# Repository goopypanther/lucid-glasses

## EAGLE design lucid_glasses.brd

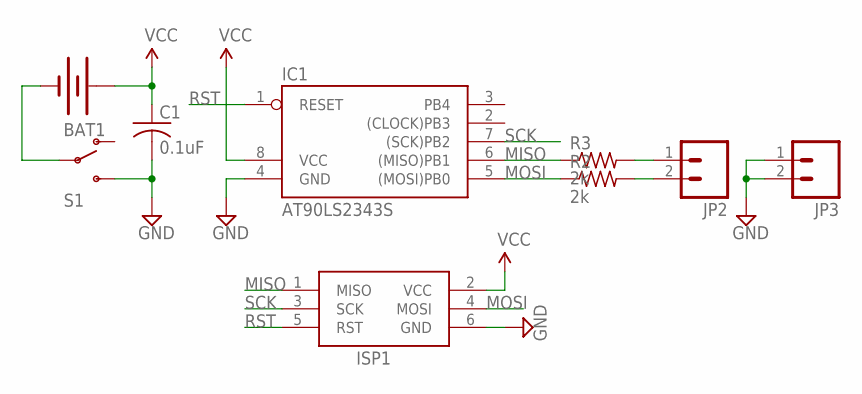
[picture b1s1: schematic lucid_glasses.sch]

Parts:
BAT1: BATTERY20SMD; BATTCON_20MM
C1: 0.1uF; C1206
IC1: AT90LS2343S; SOIC8
ISP1: AVRISP-6; AVRISP
JP2, JP3: M02PTH; 1X02
R2, R3: 2k; R1206
S1: SWITCH-SPSTSMD2; SWITCH-SPDT-SMD

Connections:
GND: C1.2, IC1.4 (GND), ISP1.6 (GND), JP3.1, JP3.2, S1.3 (S)
MISO: IC1.6 ((MISO)PB1), ISP1.1 (MISO), R3.1
MOSI: IC1.5 ((MOSI)PB0), ISP1.4 (MOSI), R2.1
unnamed: JP2.1, R3.2
unnamed: BAT1.2 (-), S1.2
unnamed: JP2.2, R2.2
RST: IC1.1 (RESET), ISP1.5 (RST)
SCK: IC1.7 ((SCK)PB2), ISP1.3 (SCK)
VCC: BAT1.1 (+), C1.1, IC1.8 (VCC), ISP1.2 (VCC)

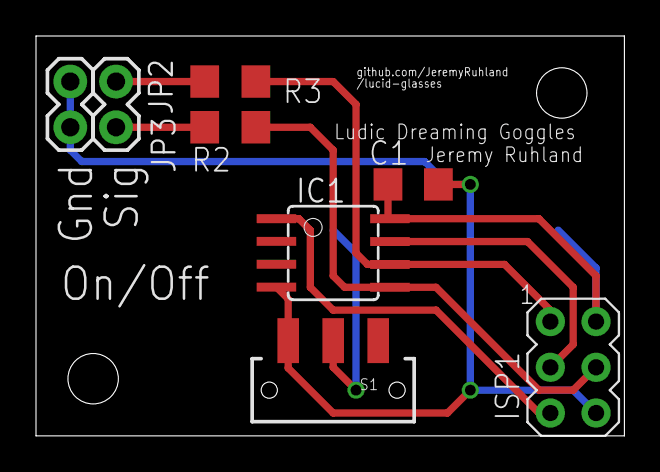
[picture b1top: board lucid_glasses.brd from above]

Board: 2 copper layers, 32.7 x 22.2 mm, 9 parts (1 on the bottom side), 9 nets.

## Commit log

2012-05-05 kinda working version
2012-05-05 working version, low speed cpu
2012-05-09 added board files
2012-05-09 added readme file
2012-05-09 added images
2012-08-08 Updated board for smt with coin cell battery.
2012-08-08 Fixed labeling issue

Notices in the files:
parts and their libraries:
sparkfun: Licensing: CC v3.0 Share-Alike You are welcome to use this library for commercial purposes.
